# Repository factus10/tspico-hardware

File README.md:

# TS-Pico hardware

Hardware for the TS-Pico, a mass-storage, ROM, and now WiFi/sound expansion card for the Timex Sinclair 2068.

## What the TS-Pico does

The TS-Pico plugs into the TS2068's rear expansion connector, with a Raspberry Pi microcontroller on the card. To the 2068 it looks like memory and I/O ports:

- **ROMs and cartridges.** The card can replace the 2068's HOME ROM and EXROM and act as a DOCK cartridge, serving the images from its own memory. It comes with its own patched 2068 ROM, which knows how to talk to the card.
- **Mass storage.** LOAD and SAVE go to files on a micro SD card instead of tape, and the card also takes `tpi:` commands. The 2068 talks to the card through I/O ports $0E/$0F.
- **Printer.** LPRINT, LLIST and COPY go to the card.

v3 adds WiFi, sound, a joystick port and a display on top of that.

## The boards

| | v2.2 | v2.5 | v2.6 | v3 |
|---|---|---|---|---|
| Status | Shipped 2023 | Prototype, not built | Prototype, not built | Proto1 built and brought up; proto3 is current |
| Controller | Raspberry Pi Pico on socket headers | Pico module soldered on its castellations (a Pico 2 fits) | RP2040 on the board, 2 MB QSPI flash, USB-C | RP2350B on the board, 16 MB QSPI flash, USB-C, PSRAM footprint (8 MB, hand-fitted) |
| Card memory | 512 KB flash (SST39SF040) + 512 KB SRAM, DIP | Same chips, SMT (PLCC flash, SOIC SRAM) | Same DIP chips, socketed | None: the RP2350B serves ROM and DOCK images from its own SRAM with PIO and DMA |
| Construction | Through-hole | All SMT, JLCPCB-assembled | SMT except the two DIP sockets | All SMT except the DE-9 and OLED header |
| Firmware | Shipped TS-Pico firmware | Runs it unchanged | Runs it unchanged | Ported (v2.3.1 runs on v3) |

**v2.2** (`old/`) is the card that shipped in September 2023. It has a Pico on headers, flash and SRAM chips, 74LS glue logic and a 555 power-on reset. The 2068 reads its ROM and cartridge images from the flash or SRAM in 16 slots of 32 KB, and the Pico switches the banks. The micro SD sits on a breakout module and shares three data lines with the bus. A jumper picks the port pair ($00-$0F or $10-$1F). The design is kept here for reference only.

**v2.5** (`hardware-v2.5/`) is the v2.2 circuit redrawn all surface mount, so JLCPCB can assemble it. It uses the v3 board outline and has a push-push micro SD socket. One block is new: **bench programming**, which lets the Pico write a blank soldered flash from USB, with no ROM programmer or 2068 needed.

**v2.6** (`hardware-v2.6/`) is the v2.2 circuit with the RP2040 chip on the board instead of a Pico module. The flash and SRAM go back to DIP-32 chips in sockets, programmed in a ROM programmer as v2.2's were. Proto2 rebuilds the glue logic in 74LVC and replaces the 555 with a TPS3808 reset supervisor.

**v3** (`hardware/`) is a redesign around the RP2350B. It keeps the firmware's view of the bus and adds:

- **Memory without memory chips.** PIO and DMA answer every Z80 memory cycle from the RP2350B's SRAM. Images live as files on the QSPI flash or the SD card, and a slot map file replaces the fixed flash banks.
- **Micro SD** on its own SPI bus, with a current-limited power switch, so a card that latches up can be power-cycled.
- **WiFi:** an ESP32-C3 running Zimodem. The card emulates the TS2050 modem's Intel 8251 at ports $73/$77.
- **Kempston joystick:** a DE-9 (Atari pinout) at port $1F.
- **Stereo audio:** PWM from the RP2350B, mixed with the 2068's SOUND line by an op-amp, out a 3.5 mm jack. It is intended for AY-3-8910 emulation, which the firmware has not scheduled yet.
- **Display:** a 128x64 SSD1309 OLED on I2C (proto3; proto1 and proto2 have a header for a 128x96 SPI module).
- **Tape:** EAR out and SPK/TAP in.
- **Bus control:** the card holds the 2068 in reset until it is ready, instead of a fixed 555 delay. There is also a /WAIT output, which the firmware does not use.
- **Power:** the card runs from the 2068's 5 V or from USB-C alone on the bench.
- **Buttons:** TS Reset, NMI, RUN and BOOTSEL.

The full spec is [docs/v3-architecture.md](docs/v3-architecture.md). Firmware progress is in [docs/v3-firmware-port-plan.md](docs/v3-firmware-port-plan.md).

## Repository

| Folder | What |
|---|---|
| `hardware/` | TS-Pico v3: KiCad 10 project. RP2350B chip-down, surface mount, JLCPCB assembly. See `hardware/README.md`; order files in [v3.0-proto3.1](https://github.com/factus10/tspico-hardware/releases/tag/v3.0-proto3.1). |
| `hardware-v2.5/` | TS-Pico v2.5: the v2.2 circuit all surface mount on the v3 outline, plus bench programming of the flash from the Pico. KiCad 10. See `hardware-v2.5/README.md`; order files in [v2.5-proto1](https://github.com/factus10/tspico-hardware/releases/tag/v2.5-proto1). |
| `hardware-v2.6/` | TS-Pico v2.6: the v2.2 circuit with the RP2040 on the board, SMT except the DIP-32 flash and SRAM (socketed, hand-soldered). KiCad 10. See `hardware-v2.6/README.md`; order files in [v2.6-proto2](https://github.com/factus10/tspico-hardware/releases/tag/v2.6-proto2). |
| `docs/` | [PLAN.md](PLAN.md) (plan), [docs/v3-architecture.md](docs/v3-architecture.md) (interface spec), part mapping, archived variants. |
| `old/` | TS-Pico v2.2: the shipped through-hole design (CircuitStudio project and full fab package, September 2023). Reference only. |

The v3 board (prototype 3). Schematic: [hardware/docs/tspico-v3-schematic.pdf](hardware/docs/tspico-v3-schematic.pdf). PCB layers: [hardware/docs/tspico-v3-pcb.pdf](hardware/docs/tspico-v3-pcb.pdf).

| v3 top | v3 bottom |
|---|---|
|  |  |

| v2.6 | v2.5 |
|---|---|
|  |  |

Firmware lives in [tspico-firmware-build](https://github.com/timex-sinclair-projects/tspico-firmware-build).

## Ordering a board

Ready-to-upload JLCPCB packages (Gerbers, BOM, placement, ordering notes, schematic PDF, renders) are attached to the GitHub releases. All are prototypes. v3 proto1 has been built and brought up (`firmware/bringup/README.md`); proto2 carries its fixes, and proto3 adds a male DE-9 for Atari sticks, a 4-pin header for an I2C SSD1309 OLED and the buttons in a 2x2 block. The others have not been built yet.

| Board | Release |
|---|---|
| v2.6: RP2040 on the board, DIP-32 flash and SRAM in sockets (hand-soldered), 74LVC glue | [v2.6-proto2](https://github.com/factus10/tspico-hardware/releases/tag/v2.6-proto2) (proto1, with 74LS glue: [v2.6-proto1](https://github.com/factus10/tspico-hardware/releases/tag/v2.6-proto1)) |
| v2.5: all surface mount, Pico module, bench programming of the flash | [v2.5-proto1](https://github.com/factus10/tspico-hardware/releases/tag/v2.5-proto1) |
| v3: RP2350B, WiFi, audio, joystick | [v3.0-proto3.1](https://github.com/factus10/tspico-hardware/releases/tag/v3.0-proto3.1): proto3 with board labels, L1 assembled (earlier: [v3.0-proto3](https://github.com/factus10/tspico-hardware/releases/tag/v3.0-proto3), no labels, L1 by hand; [v3.0-proto2.1](https://github.com/factus10/tspico-hardware/releases/tag/v3.0-proto2.1), proto2 with L1 fitted by hand; [v3.0-proto2](https://github.com/factus10/tspico-hardware/releases/tag/v3.0-proto2) assembles L1; proto1, built, before the bring-up fixes: [v3.0-proto1](https://github.com/factus10/tspico-hardware/releases/tag/v3.0-proto1)) |

## Working on the v3 hardware

Requirements: KiCad 10 (`kicad-cli` is used for checks), Python 3.

```bash
python3 hardware/scripts/gen_board.py   # regenerate the edge-connector footprint and board skeleton
hardware/scripts/check.sh               # ERC + DRC, fails on any violation
```

See `hardware/README.md` for the project layout and the geometry the edge connector is built from.

## License

The hardware designs in this repository (`hardware/`, `hardware-v2.5/`, `hardware-v2.6/`, `old/` and the design documents in `docs/`) are released under the [CERN Open Hardware Licence Version 2, Strongly Reciprocal](LICENSE) (CERN-OHL-S-2.0). You may make, modify and sell boards from them. If you distribute a modified design, or boards made from one, you must publish the modified design under the same licence.

**Source Location:** https://github.com/factus10/tspico-hardware. The v2.6 and v3 boards carry this URL, the licence name and the open-source hardware logo on their bottom silkscreen. Boards made from a modified design must carry the location of the modified source instead.

Not covered: the bring-up firmware in `firmware/` is software and is not licensed under CERN-OHL-S. `firmware/bringup/pico_sdk_import.cmake` keeps Raspberry Pi's BSD-3-Clause licence. Zimodem is fetched at build time from its own repository under its own licence. KiCad library parts and 3D models are used under the KiCad libraries' licence.

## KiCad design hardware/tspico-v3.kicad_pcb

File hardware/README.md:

# TS-Pico v3 KiCad project

Status 2026-10-19: prototype 3 ([v3.0-proto3](https://github.com/factus10/tspico-hardware/releases/tag/v3.0-proto3), changes below). Proto1 ([v3.0-proto1](https://github.com/factus10/tspico-hardware/releases/tag/v3.0-proto1)) was built and brought up; proto2 added its fixes (below). Both proto2 and proto3 were routed by `scripts/flow.py` with no hand edits, DRC clean at every severity. ERC: one warning, U4's unused input tied to GND.

**To order:** the JLCPCB upload files (Gerber zip, BOM, placement), ordering notes, schematic PDF and renders are on the [v3.0-proto3.1 release](https://github.com/factus10/tspico-hardware/releases/tag/v3.0-proto3.1): proto3 with the board labels, and L1 assembled by JLCPCB again. U22, J3 and J5 are fitted by hand. [v3.0-proto3](https://github.com/factus10/tspico-hardware/releases/tag/v3.0-proto3) is the same copper without the labels, with L1 fitted by hand. Proto2: [v3.0-proto2.1](https://github.com/factus10/tspico-hardware/releases/tag/v3.0-proto2.1) (L1 by hand) and [v3.0-proto2](https://github.com/factus10/tspico-hardware/releases/tag/v3.0-proto2) (L1 assembled by JLCPCB), same Gerbers. To regenerate them from this folder, run `python3 scripts/gen_fab.py` (output in `fab/jlcpcb/`).

## Proto4 changes (branch `claude/rp2350-inductor-replacement-f42f1a`, not yet tagged)

| Change | Parts | Why |
|---|---|---|
| External core LDO, no inductor | U33 Microne ME6211C12M5G-N (C236672), C53 1 uF input, C20 4.7 uF output; L1 removed | L1 (Abracon AOTA-B201610S3R3-101-T) ran out at JLCPCB twice (0 on 2026-10-12, 1 left on 2026-11-04) and has no substitute. RP2350 datasheet section 6.3.7 / figure 24: VREG_LX (pin 63) open, VREG_FB (pin 65) to GND, VREG_VIN and VREG_AVDD still powered for power-on reset and brown-out. DVDD is 1.2 V, the value the firmware already sets for the 250 MHz bus clock (OpenSpand does the same at 208 MHz). The ME6211 is ±1%, tighter than the on-chip regulator's ±3% at the same setting; 1.2 V is above DVDD's recommended 1.16 V and close to its 1.21 V absolute maximum, as the 1.20 V firmware setting already was. Issue #30 (does 250 MHz run at 1.1 V?) no longer blocks this; it would only matter for a 1.1 V part. |
| C31 moved | C31 left of R28 | U33 sits in its old place above the chip's top-left corner. |

Routed 2026-11-04 by `scripts/flow.py` on its first attempt with no hand edits: 2112 track segments, 401 vias, DRC clean at every severity (no errors, warnings or unconnected items), no tracks on the plane layers. ERC: the one known warning (U4). 40 BOM lines, 142 parts, $14.19/board on 10 boards with fees (proto3.1: $14.68).

Firmware for proto4: the core voltage is fixed, so `vreg_set_voltage()` has no effect (harmless). Set the VREG `HIZ` bit after boot (unlock with `VREG_CTRL.UNLOCK` first): the on-chip regulator still starts at power-up and draws about 400 µA until then. Never put the regulator in low-power mode: the datasheet says it can't be disconnected from DVDD in that mode.

## Proto3 changes

| Change | Parts | Why |
|---|---|---|
| Male DE-9 | J5 CONNFLY DS1037-09MNAKT74-0CC (C75750), footprint `DSUB-9_Pins_Horizontal_…` | Atari sticks (CX-40) end in a female plug, like the 2068's own male ports expect. Proto1/2 had a female footprint; a male connector on it mirrors every pin, putting the stick's ground (pin 8) on pin 7 (JOY_5V, open) so nothing reads. Same body position and holes as proto2. On a proto1/2 board, mount a male connector on the back of the board: turning it over puts each pin on its own pad. |
| Buttons and LED moved | SW3 under SW1, SW4 under SW2; D4/R5 left of the ESP32 | A 1.54 in module on J3 covered BOOTSEL and crowded RUN. |
| I2C OLED header | J3 1x4 (1 GND, 2 +3V3, 3 SCL, 4 SDA), R44/R45 4k7 pull-ups | For a 1.54 in 128x64 SSD1309 I2C module, on I2C1 (GP43 SCL, GP42 SDA). Replaces the 7-pin header for the 1.27 in SSD1351 SPI module. GP34, GP41 and expander P0.2 (with its pull-down R11) are freed. |

## Proto2 changes (from proto1 bring-up and issue #21)

| Change | Parts | Why |
|---|---|---|
| nBE pull-up to +5V_EDGE | R14 2k2 | The 74LVC06 only pulls /BE low; without a pull-up it rose too slowly and a RAM opcode fetch after a served byte read wrong bits. Proto1 boards carry a 2.2k bodge from A29 to +5V. |
| GP8-GP10 pull-ups | R15-R17 10k | nAEN_LO, nAEN_HI, nDATA_OE: the RP2350 resets its pads with pull-downs, so in reset and BOOTSEL all three buffers were enabled and U1/U2 fought on MD. |
| SD socket power switch | U32 SY6280AAC, R42 15k (0.45 A), R43 10k, C52 1u | Socket VDD is now +3V3_SD, switched from XL9555 P0.6 (SD_PWR_EN, off at power-up). A latched card hits the current limit instead of resetting the RP2350B; the firmware can power-cycle a card. R34-R37 moved to +3V3_SD; R38 (detect) stays on +3V3. |
| U22 footprint | SOIC-8 3.9 x 4.9 mm | The APS6404L-3SQR-SN is SOP-8 150 mil (AP Memory package code SN); proto1 had the 208 mil footprint. Still DNP; see `docs/bom-cost-optimization.md` for PSRAM options. |
| L1 fitted by hand | L1 DNP at JLCPCB | The RP2350 core-regulator inductor (Abracon AOTA-B201610S3R3-101-T) was out of stock at JLCPCB and LCSC on 2026-10-12. Raspberry Pi names no substitute: it is the only polarity-marked 0806 part. Fit it with the dot on pad 2 (DVDD, silkscreen dot), the end away from the top edge; the core has no supply until it is on. Gerbers unchanged. From proto3.1 (2026-10-22, 326 in stock) JLCPCB assembles it again. |

Firmware for proto2: set SD_PWR_EN (expander port 0 bit 6) after the detect switch reads a card and before any SPI; return the SD pins to inputs before clearing it.

Sheets are generated by `scripts/gen_<sheet>.py` on top of `scripts/schlib.py`, netlist-style (labels on every pin, no wires). Regenerating a sheet overwrites hand edits, so once a sheet is being edited in KiCad, retire its generator. Spec: [../docs/v3-architecture.md](../docs/v3-architecture.md).

## Files

| File | Purpose |
|---|---|
| `tspico-v3.kicad_pro` | Project. Design rules are JLCPCB 4-layer capable but conservative: 0.127 mm min clearance and track, 0.45/0.2 mm min via, 0.3 mm copper-to-edge. Net classes: Default 0.2 mm track / 0.6-0.3 via, Power 0.5 mm / 0.8-0.4. |
| `tspico-v3.kicad_sch` | Root sheet with eight hierarchical sheets: `interface`, `memory`, `mcu`, `power`, `storage_display`, `wifi`, `audio`, `joystick`. |
| `tspico-v3.kicad_pcb` | 4-layer board (F.Cu, In1 GND, In2 PWR, B.Cu), 1.6 mm, ENIG. Outline and connector generated by `scripts/gen_board.py`. |
| `lib/tspico.pretty/TS2068_EdgeConnector_2x32.kicad_mod` | The 2068 edge connector (generated). |
| `lib/tspico.kicad_sym` | Project symbols (empty so far; ESP32-C3 module and anything not in the stock library go here). |
| `scripts/gen_board.py` | Regenerates the edge-connector footprint and the bare board skeleton (outline, connector, holes, fiducials). Called by `gen_layout.py`. |
| `scripts/gen_layout.py` | Builds the placed board: exports the netlist, loads every footprint from the KiCad or project library, assigns nets, places parts from its `P` table, adds the GND and +3V3 zones. Run with KiCad's bundled Python (`/Applications/KiCad/KiCad.app/Contents/Frameworks/Python.framework/Versions/Current/bin/python3`). **It overwrites `tspico-v3.kicad_pcb`, so once routing starts in KiCad, stop running it and treat the placement table as history.** |
| `scripts/check.sh` | `kicad-cli` ERC and DRC. |
| `scripts/schlib.py`, `scripts/gen_edge_symbol.py`, `scripts/gen_interface.py`, `scripts/gen_memory.py`, `scripts/gen_mcu.py`, `scripts/gen_power.py`, `scripts/gen_storage_display.py`, `scripts/gen_wifi.py`, `scripts/gen_audio.py`, `scripts/gen_joystick.py` | Schematic generators (see above). |
| `scripts/parts.py` | Orderable part table: (Value, footprint) to MPN and LCSC number. `schlib.place()` stamps MPN and LCSC fields on every symbol from it. |
| `bom/tspico-v3-jlcpcb-bom.csv` | JLCPCB-format BOM (Comment, Designator, Footprint, LCSC Part #), regenerated by the command below. |
| `bom/tspico-v3-bom-full.csv` | Same grouping with MPN and quantities. |
| `docs/tspico-v3-schematic.pdf` | Schematic, all nine sheets. |
| `docs/tspico-v3-pcb.pdf` | PCB plot, one page per layer: F.Cu, In1.Cu, In2.Cu, B.Cu, F/B silkscreen, F/B fab (DNP parts crossed out). Bottom layers are not mirrored. |
| `renders/` | 3D renders (top, bottom, isometric). |
| `fab/` | Plot output directory (ignored by git). |

## Edge connector geometry

Measured from the v2.2 fab Gerbers (`../old/tsPico2_2Fab/Gerber/tsPico.GTL`, `.GBL`, `.Outline`):

| Item | Value |
|---|---|
| Board | 130.00 x 64.25 mm, 1.6 mm (v2.2 was 100 mm tall; v3 body is 56 mm plus the 8.25 mm tongue) |
| Body | 130.00 x 64.00 mm |
| Tongue | 83.66 mm wide, 8.25 mm deep, left edge 18.48 mm from the board's left edge, 1.0 mm corner chamfers |
| Positions | 32 at 2.54 mm pitch, 31 fingers per side |
| Keying slot | position 6, 2.03 mm wide, 8.26 mm deep |
| Fingers | 1.651 x 8.255 mm (65 x 325 mil), first finger centre 2.52 mm from the tongue's left edge, bottom edge 0.32 mm above the tongue edge |

Pad names are `A1`..`A32` on F.Cu and `B1`..`B32` on B.Cu (no A6/B6), following the TS2068 Technical Manual table 2.4.1-1. Position 1 is at the left when the board is viewed from the top with the connector at the bottom.

**Side A is the top (component) side, confirmed:** side A (GND, EAR, D7, ..., SOUND) is on the top and side B (+15V, +5V, address bus, video) on the bottom. Proto1 proved it in a 2068 on 2026-10-07 ([`firmware/bringup/README.md`](../firmware/bringup/README.md)). In shadow mode it logged every address the Z80 read through the side-B fingers, the boot log matching the ROM exactly. It then served the HOME ROM onto side A, with /MREQ and /RD timing each read, /BE on A29 and the data on D0-D7, and the 2068 booted to the card's "TS-Pico v3 ROM" banner. With the sides swapped, the address fingers would sit on data and control lines and none of that could work. This also matches how the v2.2 layout routes +5V (bottom trace from the fourth finger).

Fab notes for the fingers: hard gold over the fingers if the fab offers it (ENIG otherwise), 30 degree bevel on the tongue edge, no copper within 0.3 mm of the slot.

## Stock library parts already identified

RP2350B symbol (`MCU_RaspberryPi`), `Package_DFN_QFN:QFN-80-1EP_10x10mm_P0.4mm_EP3.4x3.4mm`, `TSPico:microSD_TF-01A` (to be drawn from the HRO TF-01A drawing), `Connector_Dsub:DSUB-9_*`, `Connector_USB:USB_C_Receptacle_HRO_TYPE-C-31-M-12`, SOIC/TSSOP logic packages, `Button_Switch_SMD:SW_SPST_PTS645Sx43SMTR92`, `Connector_Audio:Jack_3.5mm_CUI_SJ-352x-SMT_Horizontal`, `Crystal:Crystal_SMD_3225-4Pin_3.2x2.5mm`.

All parts used so far have stock symbols and footprints (the APS6404L PSRAM is in `Memory_RAM`, the ESP32-C3-WROOM-02 in `RF_Module`).

## Regenerating the BOM

```bash
cd hardware
KC=/Applications/KiCad/KiCad.app/Contents/MacOS/kicad-cli
$KC sch export bom --output bom/tspico-v3-jlcpcb-bom.csv --fields "Value,Reference,Footprint,LCSC" --labels "Comment,Designator,Footprint,LCSC Part #" --group-by "Value,Footprint" --exclude-dnp tspico-v3.kicad_sch
```

Part choices are priced against JLCPCB's catalog with `python3 scripts/jlc_price.py --boards 10`; the reasoning for each substitution is in `docs/bom-cost-optimization.md` (2026-09-17: parts + fees per board went from $32.95 to $14.93 on a 10-board run, to $14.48 after the DMA option was dropped; fitted logic packages from 16 to 7). The board was laid out again for these parts on 2026-09-17 (see the routing section).

## Fab outputs

`python3 scripts/gen_fab.py` writes `fab/jlcpcb/`: `tspico-v3-gerbers.zip` (4-layer Gerbers + Excellon drill), `tspico-v3-bom.csv` and `tspico-v3-cpl.csv` (JLCPCB assembly format), and refreshes the two BOMs in `bom/`. `fab/NOTES.md` lists what to check on upload (rotations of QFN/SOT/connector parts need checking in JLC's placement preview; J3 and J5 are through-hole).

## Schematic and PCB PDFs, renders

Regenerate after a board or schematic change (from `hardware/`):

```bash
KC=/Applications/KiCad/KiCad.app/Contents/MacOS/kicad-cli
$KC sch export pdf -o docs/tspico-v3-schematic.pdf tspico-v3.kicad_sch
$KC pcb export pdf --mode-multipage --ibt --scale 0 --cdnp -l F.Cu,In1.Cu,In2.Cu,B.Cu,F.Silkscreen,B.Silkscreen,F.Fab,B.Fab --cl Edge.Cuts -o docs/tspico-v3-pcb.pdf tspico-v3.kicad_pcb
$KC pcb render --side top --quality high -w 2384 -h 1376 --zoom 1.1 -o renders/tspico-v3-top.png tspico-v3.kicad_pcb
$KC pcb render --side bottom --quality high -w 2384 -h 1376 --zoom 1.1 -o renders/tspico-v3-bottom.png tspico-v3.kicad_pcb
$KC pcb render --side top --quality high -w 2384 -h 1568 --rotate '-45,0,45' --perspective -o renders/tspico-v3-iso.png tspico-v3.kicad_pcb
```

Parts without a 3D model in the KiCad library (the four buttons, USB-C, micro SD socket, audio jack) show as bare pads in the renders; U22 is DNP.

## Layout notes

- Body 130 x 56 mm (the register row of the first layout is gone). Left edge, top to bottom: ESP32-C3 antenna, USB-C, micro SD. The TF-01A socket's shell is flush with the board edge (its shield pads sit 3 mm back, so nothing needs edge clearance). Right edge: 3.5 mm jack in the corner, DE-9 below it.
- Top edge: buttons in a 2x2 block on 0.5 in centres (top row TS Reset, NMI; below them RUN, BOOTSEL; proto1/2 had all four in a row), then the OLED header. The module on J3 covers everything right of the buttons, so nothing there may be taller than its standoff. The LED (D4, R5) sits left of the ESP32, between the mounting hole and the USB-C socket. A bottom-layer keepout (no tracks or vias) sits under the RP2350B.
- Row above the fingers: data U3, high address byte U2 directly over fingers A15-A8, control U4 (U3 is turned 180 degrees from the others: its A side is the Z80 side so DIR can be /RD itself). Row above that: low address byte U1 over U2, fed from fingers A0-A3 on the left and A7-A4 on the right along the bottom layer, then strobe OR gates U6 and open-drain drivers U7. Both address buffers put plain bytes on MD0-MD7, so the firmware sees ordinary addresses. I2C expander U15 and the joystick conditioning network sit beside the DE-9; audio and the two LDOs above them.
- RP2350B core supply (proto4): the ME6211C12 LDO U33 sits above the chip's top-left corner, input cap C53 to its right, output cap C20 to its left. Its 0.3 mm output track drops straight down beside R28 and enters the pad ring diagonally at the corner between pins 60 and 61, joining the DVDD spine under the package. VREG_LX is open, VREG_FB runs to the PGND via, VIN goes straight into C22 and the AVDD filter R28/C39 sits above, as in "Hardware design with RP2350" figure 4. (Proto1-3 had the design guide's switcher with L1 left of C20/C22.)
- Crystal 6.5 mm from its pins with R20 between chip and crystal; XOUT_R runs under the crystal to pad 3. XIN and XOUT drop one pad lane after leaving the chip so DVDD pin 32 has room for its via.
- Before ordering: check the D-sub footprint against the CONNFLY DS1037 drawing, check `lib/tspico.pretty/microSD_TF-01A` against the part's drawing (generated from LCSC's land pattern). (TF-01A card detect: low = card in, confirmed on proto1.)

## Routing flow and state

```bash
cd hardware
PY=/Applications/KiCad/KiCad.app/Contents/Frameworks/Python.framework/Versions/Current/bin/python3
$PY scripts/gen_layout.py     # placement, keepouts, planes (discards all routing)
$PY scripts/preroute.py       # locked hand routes: core LDO and regulator pins, crystal, DVDD spine, inner supply links, bottom-row fan
$PY scripts/autoroute.py --passes 100     # jar from $FREEROUTING_JAR (or --jar); about 25 minutes
$PY scripts/finish.py         # widen necked tracks, join orphan supply islands, retry open nets, drop unused vias and stubs
$PY scripts/silk.py           # place reference designators clear of pads, silk and the edge; trim outlines at the edge
$PY scripts/labels.py v3      # board name on top; name, URL, licence and OSHW logo on the bottom
```

Or all five in one command, which is the way to run it:

```bash
$PY scripts/flow.py                       # jar from $FREEROUTING_JAR (or --jar); 10 to 15 minutes per attempt, up to 3 attempts
```

Freerouting does not give the same result twice from the same input. Before U1's address pins had their pre-routed via fan (below), about one run in three left one of them (A3, A5) sealed in behind its neighbours' vias; with the fan, three runs out of three closed on the first attempt. The safety net stays: if a signal net is left open, `finish.py` tries lifting the neighbours' copper around the pin, routing the open net and putting the neighbours back, but refuses a result that needs more than three vias per net (the only way out of such a pocket has been a 9-via, 70 mm detour). If the board still is not clean `finish.py` exits non-zero and `flow.py` routes again from the placement, keeping the failed board as `fab/route/attempt-N.kicad_pcb`.

Rules: 0.15 mm signal tracks (the router may neck down to 0.11 mm in a squeeze; board minimum 0.1 mm, JLCPCB's is 0.09), 0.4 mm on the 5 V rails and +3V3_WIFI, 0.127 mm clearance, every via 0.6/0.3 mm (JLCPCB's no-surcharge size; the ESP32 footprint's 0.2 mm thermal vias are opened to 0.3 mm by `gen_layout.py`). The pre-stitch step skips the RP2350B's pins: a via 0.9 mm out of a 0.4 mm pitch pin blocks both neighbours' escape lanes. Its exposed pad gets five ground vias.

What `preroute.py` fixes in place before the autorouter runs, because the router handles a fully used 0.4 mm pitch QFN badly (whichever pins it leaves for last end up sealed behind its own vias):

- the core LDO and the on-chip regulator's pins, and the crystal, as above;
- the **DVDD spine**: 0.25 mm track under the package from the LDO's entry at the top-left corner to DVDD pins 51, 10 and 32 (only the first 3 mm at the pins is 0.15 mm), and pin 51's 100 nF 2 mm from its pin;
- the 3.3 V supply pins linked in groups under the package, each group with one via: 50 to corner pin 41, 68/69 to 76 to pin 5, 24 to 29;
- the **bottom pad row** (pins 1-20, all used) as a deterministic fan: straight out to a staggered depth, a 45 degree turn, and a via on a common line at 0.75 mm spacing, which is the tightest legal pattern for 0.6 mm vias at 0.4 mm pitch.
- **U1's Z80-side pins** (A0-A7): each runs straight in under U1's body to its own via, in two staggered rows 1.26 and 2.06 mm from the pads. U1's bottom pad row faces U2's top row across a 0.8 mm gap, so these pins can only leave under U1, and their fingers are on the bottom layer, so each needs a via anyway. Neighbouring vias are 1.03 mm apart, and a track on either layer still passes between two vias of the near row.

State on 2026-09-17 (DMA option dropped, address buffers delivering plain bytes, audio and joystick passives respaced for silkscreen, U1 address fan pre-routed): **fully routed, DRC clean at every severity (no errors, no warnings, no unconnected items)**, no tracks on either plane layer. 2073 track segments, 378 vias, all 0.6/0.3 mm, no track under 0.13 mm. Produced by `flow.py` on its first attempt with no hand edits. (Run DRC on the board where it sits: a copy outside the project folder is checked against KiCad's default rules and reports hundreds of false clearance errors.)

Silkscreen: `silk.py` sets designators to 0.8 mm text and tries positions around each part until one clears pads, other silk, other parts and the board edge; rows of equal parts all get the label on the same side (above a flat part, to the right of an upright one), and a hidden designator gets a second chance by moving a neighbour's. The layout leaves room for this: passive rows are 3.2 mm apart in the audio block, 2.7 mm in the SD pull-ups, and the joystick RC columns are 2.6 mm apart. 139 of 140 designators are on silk; only C39 (the VREG_AVDD capacitor, boxed in by the design guide's regulator layout) is hidden, and it is on F.Fab with all the others. Outlines of edge connectors that overhang the board are trimmed where they cross the edge.

Board labels: `labels.py` (also run by `flow.py`) puts "TS-Pico v3" on the top silkscreen above the left end of the fingers. On the bottom it puts the name, the repository URL (the CERN-OHL-S Source Location), the licence and the OSHW logo. It only touches its own group of silkscreen items, so it can be rerun on a routed board, and it refuses to save if a label would land on a pad, a courtyard or other silk. `labels.py v2.6` does the same for `../hardware-v2.6/`.

Rerunning `autoroute.py` continues from the current routing (it exports existing tracks); `--fresh` starts over. Do not rerun `gen_layout.py`: it rebuilds the board from placement and discards routing.

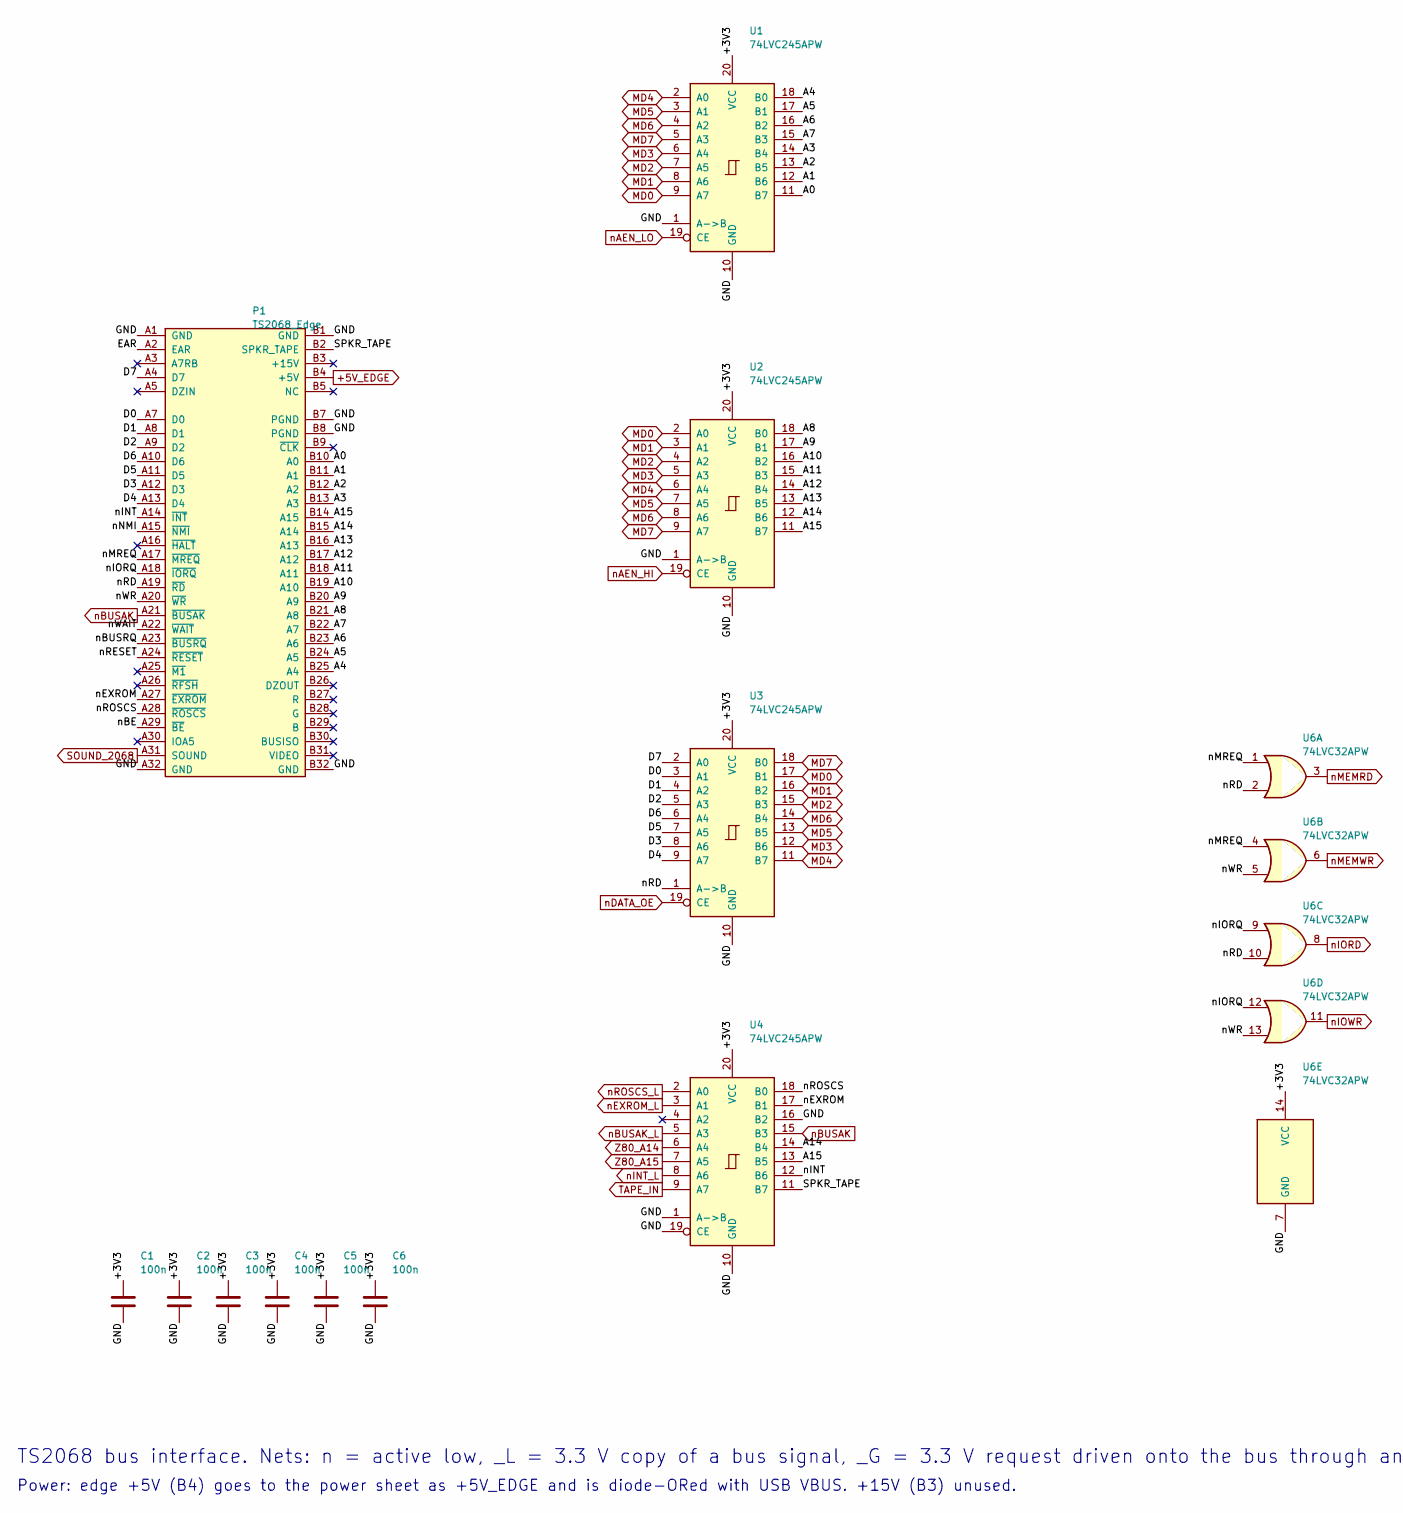
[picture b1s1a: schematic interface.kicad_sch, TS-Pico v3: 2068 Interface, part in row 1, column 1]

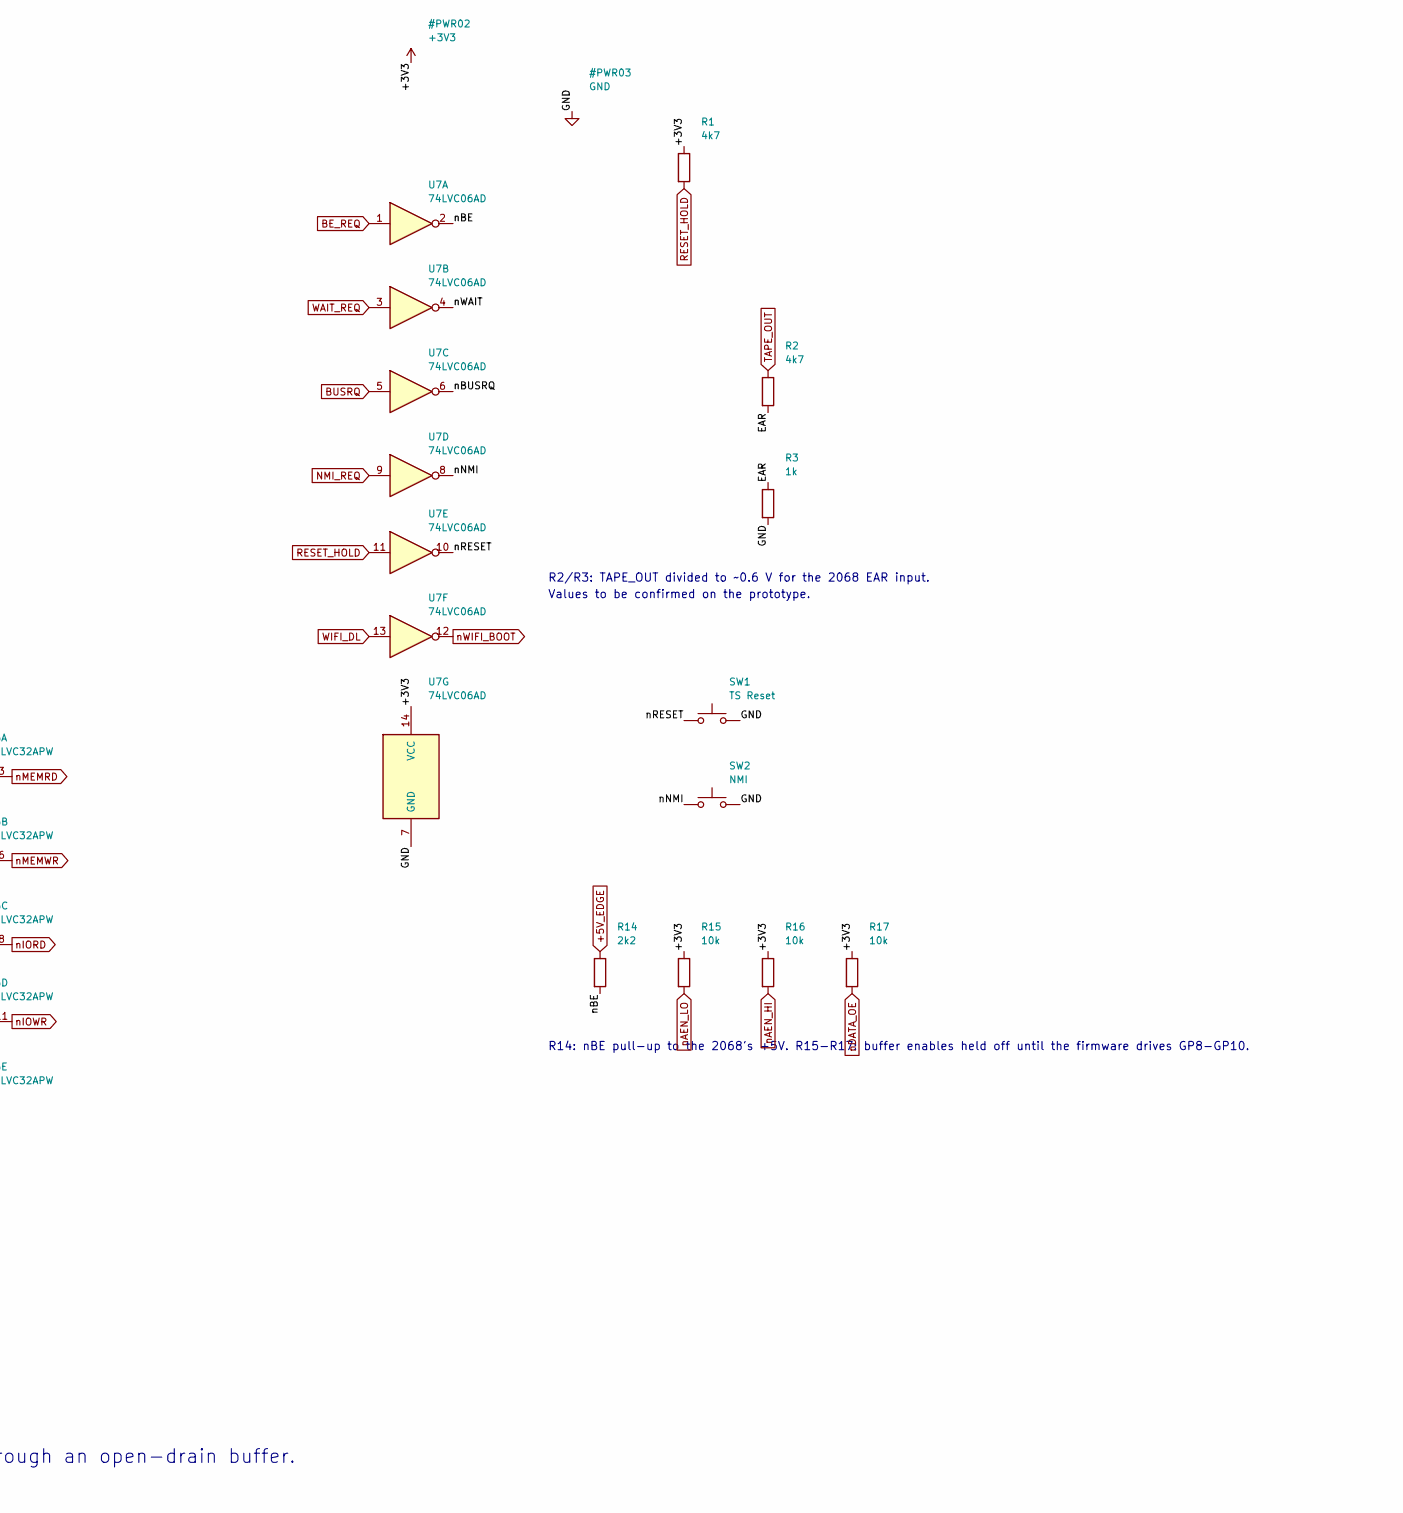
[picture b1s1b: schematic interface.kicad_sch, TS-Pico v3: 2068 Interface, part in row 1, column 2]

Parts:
C1, C2, C3, C4, C5, C6: 100n; C_0603_1608Metric; MPN CC0603KRX7R9BB104; LCSC C14663
P1: TS2068_Edge; TS2068_EdgeConnector_2x32
R1, R2: 4k7; R_0603_1608Metric; MPN 0603WAF4701T5E; LCSC C23162
R3: 1k; R_0603_1608Metric; MPN 0603WAF1001T5E; LCSC C21190
R14: 2k2; R_0603_1608Metric; MPN 0603WAF2201T5E; LCSC C4190
R15, R16, R17: 10k; R_0603_1608Metric; MPN 0603WAF1002T5E; LCSC C25804
SW1: TS Reset; SW_Push_1P1T_XKB_TS-1187A; MPN TS-1187A-B-A-B; LCSC C318884
SW2: NMI; SW_Push_1P1T_XKB_TS-1187A; MPN TS-1187A-B-A-B; LCSC C318884
U1, U2, U3, U4: 74LVC245APW; TSSOP-20_4.4x6.5mm_P0.65mm; MPN 74LVC245APW,118; LCSC C6082
U6: 74LVC32APW; TSSOP-14_4.4x5mm_P0.65mm; MPN 74LVC32APW,118; LCSC C6087
U7: 74LVC06AD; SOIC-14_3.9x8.7mm_P1.27mm; MPN EM74LVC06AD; LCSC C49188178

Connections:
+3V3: C1.1, C2.1, C3.1, C4.1, C5.1, C6.1, R1.1, R15.1, R16.1, R17.1, U1.20 (VCC), U2.20 (VCC), U3.20 (VCC), U4.20 (VCC), U6.14 (VCC), U7.14 (VCC); also elsewhere on the board
+5V_EDGE: P1.B4 (+5V), R14.1; also elsewhere on the board
/2068 Interface/A0: P1.B10 (A0), U1.11 (B7)
/2068 Interface/A1: P1.B11 (A1), U1.12 (B6)
/2068 Interface/A2: P1.B12 (A2), U1.13 (B5)
/2068 Interface/A3: P1.B13 (A3), U1.14 (B4)
/2068 Interface/A4: P1.B25 (A4), U1.18 (B0)
/2068 Interface/A5: P1.B24 (A5), U1.17 (B1)
/2068 Interface/A6: P1.B23 (A6), U1.16 (B2)
/2068 Interface/A7: P1.B22 (A7), U1.15 (B3)
/2068 Interface/A8: P1.B21 (A8), U2.18 (B0)
/2068 Interface/A9: P1.B20 (A9), U2.17 (B1)
/2068 Interface/A10: P1.B19 (A10), U2.16 (B2)
/2068 Interface/A11: P1.B18 (A11), U2.15 (B3)
/2068 Interface/A12: P1.B17 (A12), U2.14 (B4)
/2068 Interface/A13: P1.B16 (A13), U2.13 (B5)
/2068 Interface/A14: P1.B15 (A14), U2.12 (B6), U4.14 (B4)
/2068 Interface/A15: P1.B14 (A15), U2.11 (B7), U4.13 (B5)
/2068 Interface/D0: P1.A7 (D0), U3.3 (A1)
/2068 Interface/D1: P1.A8 (D1), U3.4 (A2)
/2068 Interface/D2: P1.A9 (D2), U3.5 (A3)
/2068 Interface/D3: P1.A12 (D3), U3.8 (A6)
/2068 Interface/D4: P1.A13 (D4), U3.9 (A7)
/2068 Interface/D5: P1.A11 (D5), U3.7 (A5)
/2068 Interface/D6: P1.A10 (D6), U3.6 (A4)
/2068 Interface/D7: P1.A4 (D7), U3.2 (A0)
/2068 Interface/EAR: P1.A2 (EAR), R2.2, R3.1
/2068 Interface/SPKR_TAPE: P1.B2 (SPKR_TAPE), U4.11 (B7)
/2068 Interface/nBE: P1.A29 (~BE), R14.2, U7.2
/2068 Interface/nBUSRQ: P1.A23 (~BUSRQ), U7.6
/2068 Interface/nEXROM: P1.A27 (~EXROM), U4.17 (B1)
/2068 Interface/nINT: P1.A14 (~INT), U4.12 (B6)
/2068 Interface/nIORQ: P1.A18 (~IORQ), U6.9, U6.12
/2068 Interface/nMREQ: P1.A17 (~MREQ), U6.1, U6.4
/2068 Interface/nNMI: P1.A15 (~NMI), SW2.1, U7.8
/2068 Interface/nRD: P1.A19 (~RD), U3.1 (A->B), U6.2, U6.10
/2068 Interface/nRESET: P1.A24 (~RESET), SW1.1, U7.10
/2068 Interface/nROSCS: P1.A28 (~ROSCS), U4.18 (B0)
/2068 Interface/nWAIT: P1.A22 (~WAIT), U7.4
/2068 Interface/nWR: P1.A20 (~WR), U6.5, U6.13
BE_REQ: U7.1; also elsewhere on the board
BUSRQ: U7.5; also elsewhere on the board
MD0: U1.9 (A7), U2.2 (A0), U3.17 (B1); also elsewhere on the board
MD1: U1.8 (A6), U2.3 (A1), U3.16 (B2); also elsewhere on the board
MD2: U1.7 (A5), U2.4 (A2), U3.15 (B3); also elsewhere on the board
MD3: U1.6 (A4), U2.5 (A3), U3.12 (B6); also elsewhere on the board
MD4: U1.2 (A0), U2.6 (A4), U3.11 (B7); also elsewhere on the board
MD5: U1.3 (A1), U2.7 (A5), U3.13 (B5); also elsewhere on the board
MD6: U1.4 (A2), U2.8 (A6), U3.14 (B4); also elsewhere on the board
MD7: U1.5 (A3), U2.9 (A7), U3.18 (B0); also elsewhere on the board
NMI_REQ: U7.9; also elsewhere on the board
RESET_HOLD: R1.2, U7.11; also elsewhere on the board
SOUND_2068: P1.A31 (SOUND); also elsewhere on the board
TAPE_IN: U4.9 (A7); also elsewhere on the board
TAPE_OUT: R2.1; also elsewhere on the board
WAIT_REQ: U7.3; also elsewhere on the board
WIFI_DL: U7.13; also elsewhere on the board
Z80_A14: U4.6 (A4); also elsewhere on the board
Z80_A15: U4.7 (A5); also elsewhere on the board
nAEN_HI: R16.2, U2.19 (CE); also elsewhere on the board
nAEN_LO: R15.2, U1.19 (CE); also elsewhere on the board
nBUSAK: P1.A21 (~BUSAK), U4.15 (B3)
nBUSAK_L: U4.5 (A3); also elsewhere on the board
nDATA_OE: R17.2, U3.19 (CE); also elsewhere on the board
nEXROM_L: U4.3 (A1); also elsewhere on the board
nINT_L: U4.8 (A6); also elsewhere on the board
nIORD: U6.8; also elsewhere on the board
nIOWR: U6.11; also elsewhere on the board
nMEMRD: U6.3; also elsewhere on the board
nMEMWR: U6.6; also elsewhere on the board
nROSCS_L: U4.2 (A0); also elsewhere on the board
nWIFI_BOOT: U7.12; also elsewhere on the board

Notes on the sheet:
TS2068 bus interface. Nets: n = active low, _L = 3.3 V copy of a bus signal, _G = 3.3 V request driven onto the bus through an open-drain buffer.
Power: edge +5V (B4) goes to the power sheet as +5V_EDGE and is diode-ORed with USB VBUS. +15V (B3) unused.
R2/R3: TAPE_OUT divided to ~0.6 V for the 2068 EAR input.
Values to be confirmed on the prototype.
R14: nBE pull-up to the 2068's +5V. R15-R17: buffer enables held off until the firmware drives GP8-GP10.

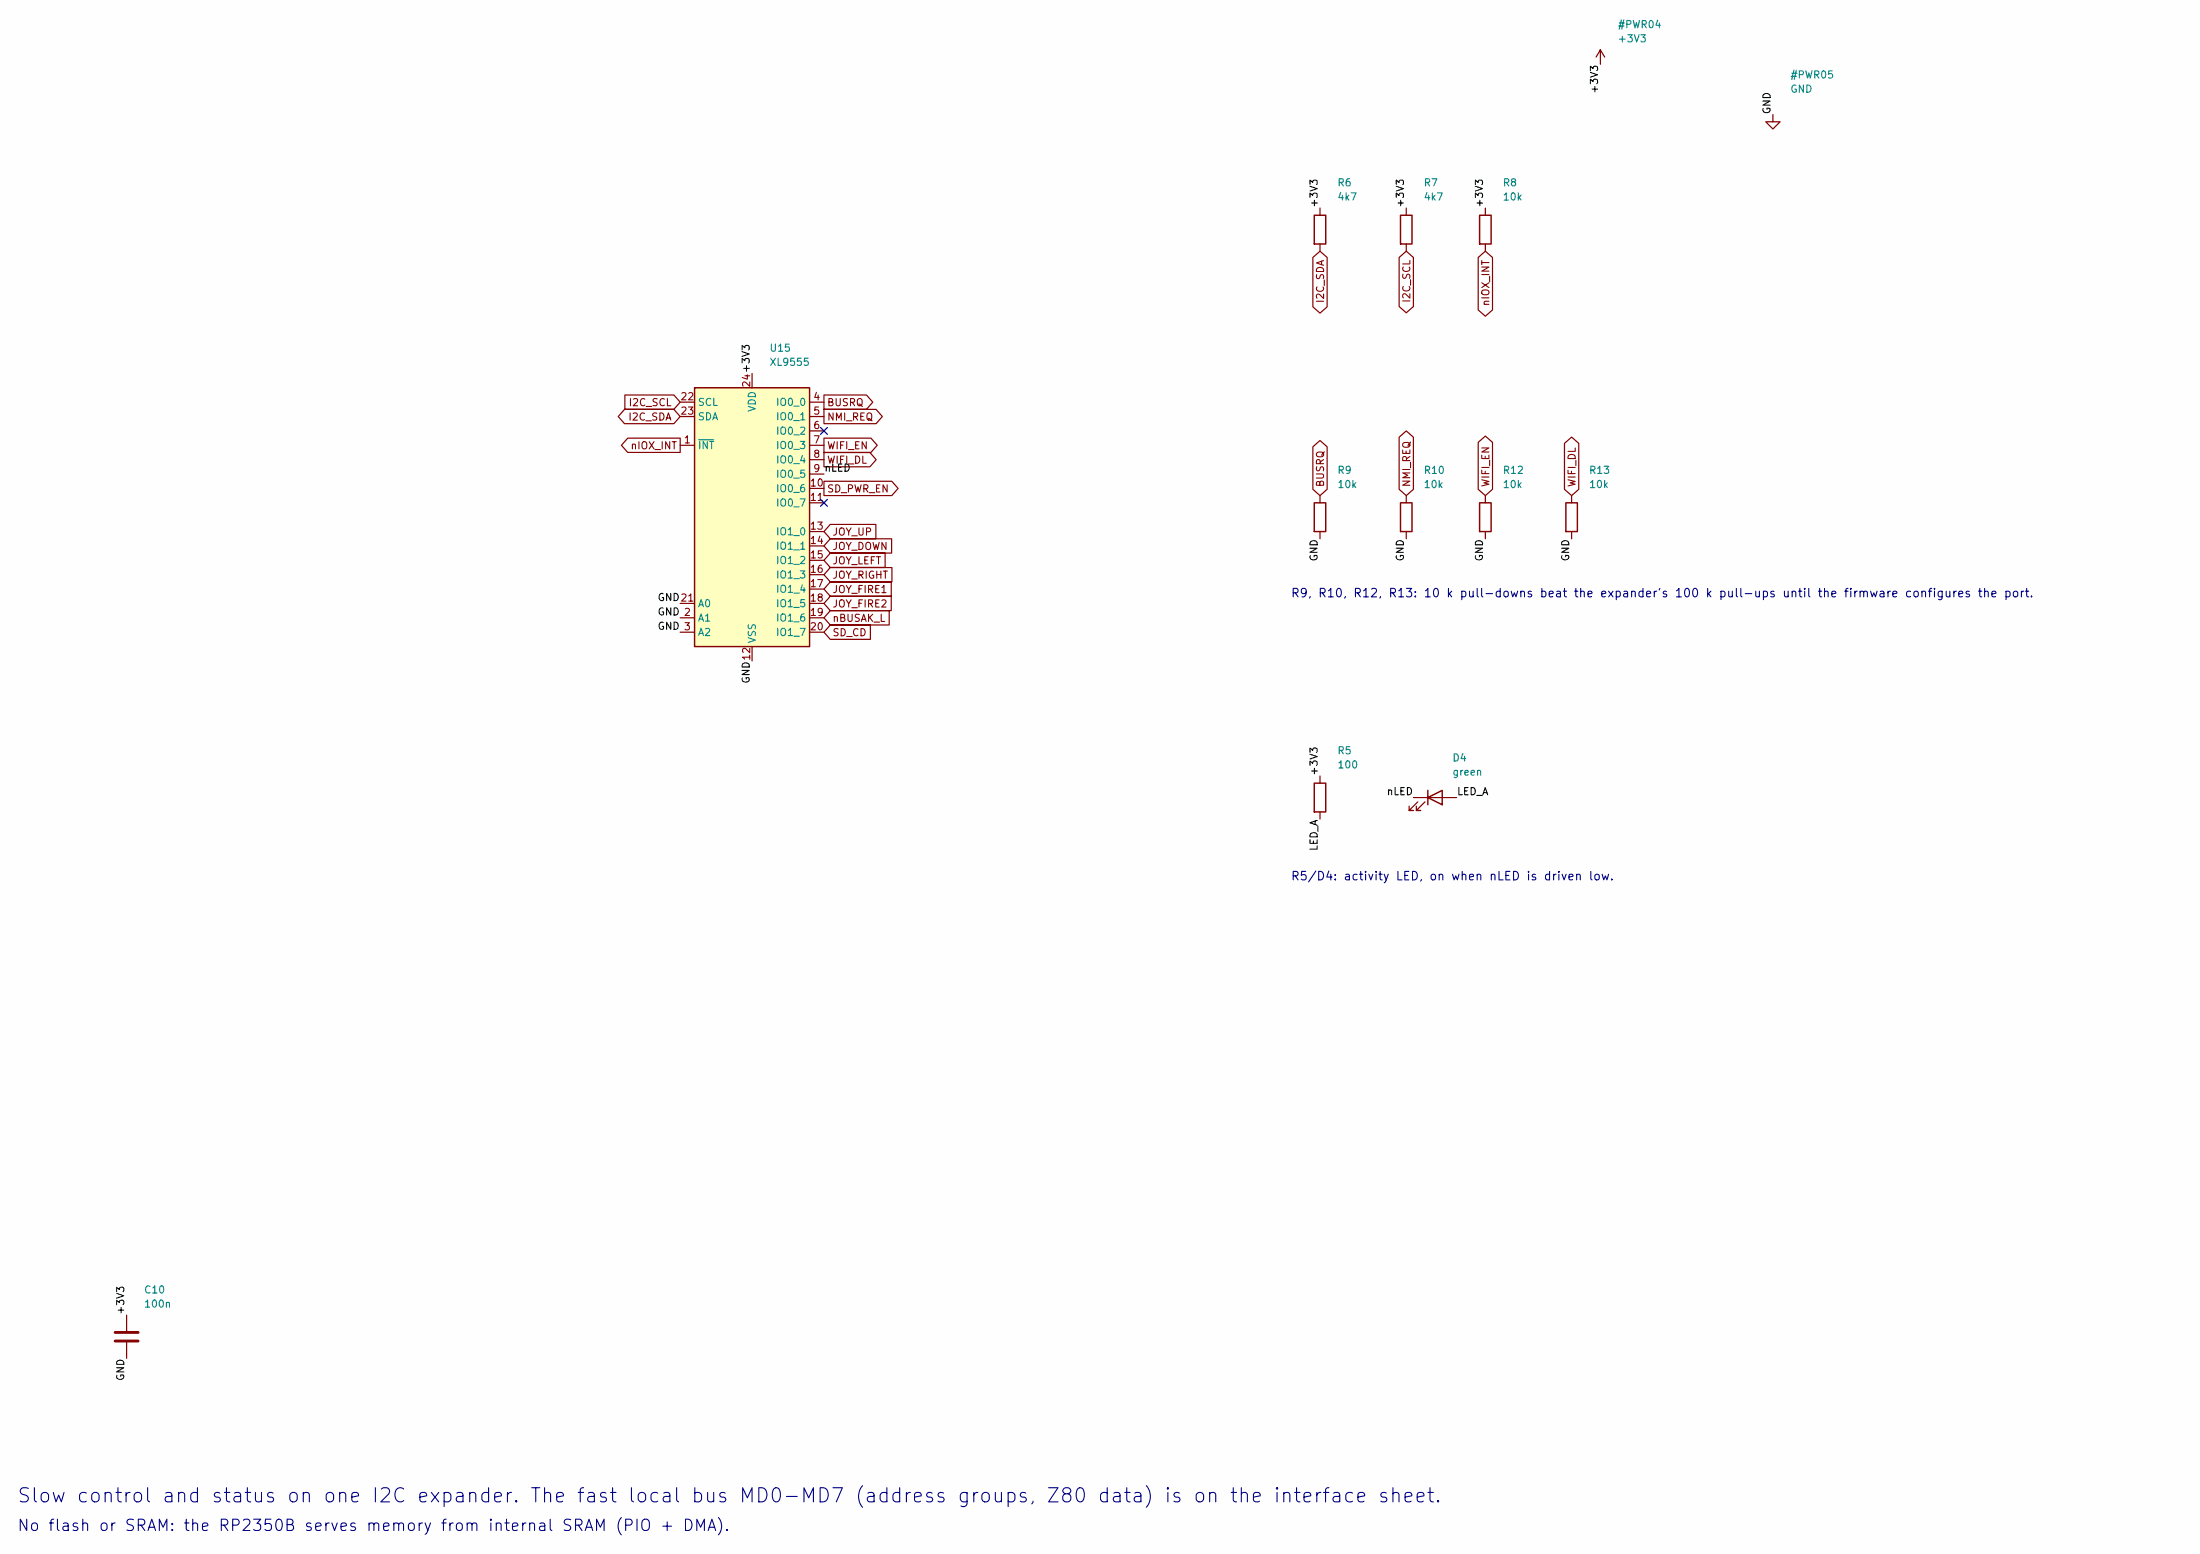
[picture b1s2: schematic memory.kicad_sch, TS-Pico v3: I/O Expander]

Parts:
C10: 100n; C_0603_1608Metric; MPN CC0603KRX7R9BB104; LCSC C14663
D4: green; LED_0805_2012Metric; MPN KT-0805G; LCSC C2297
R5: 100; R_0603_1608Metric; MPN 0603WAF1000T5E; LCSC C22775
R6, R7: 4k7; R_0603_1608Metric; MPN 0603WAF4701T5E; LCSC C23162
R8, R9, R10, R12, R13: 10k; R_0603_1608Metric; MPN 0603WAF1002T5E; LCSC C25804
U15: XL9555; TSSOP-24_4.4x7.8mm_P0.65mm; MPN XL9555; LCSC C609791

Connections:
+3V3: C10.1, R5.1, R6.1, R7.1, R8.1, U15.24 (VDD); also elsewhere on the board
/Local Bus and Registers/LED_A: D4.2 (A), R5.2
/Local Bus and Registers/nLED: D4.1 (K), U15.9 (IO0_5)
BUSRQ: R9.1, U15.4 (IO0_0); also elsewhere on the board
I2C_SCL: R7.2, U15.22 (SCL); also elsewhere on the board
I2C_SDA: R6.2, U15.23 (SDA); also elsewhere on the board
JOY_DOWN: U15.14 (IO1_1); also elsewhere on the board
JOY_FIRE1: U15.17 (IO1_4); also elsewhere on the board
JOY_FIRE2: U15.18 (IO1_5); also elsewhere on the board
JOY_LEFT: U15.15 (IO1_2); also elsewhere on the board
JOY_RIGHT: U15.16 (IO1_3); also elsewhere on the board
JOY_UP: U15.13 (IO1_0); also elsewhere on the board
NMI_REQ: R10.1, U15.5 (IO0_1); also elsewhere on the board
SD_CD: U15.20 (IO1_7); also elsewhere on the board
SD_PWR_EN: U15.10 (IO0_6); also elsewhere on the board
WIFI_DL: R13.1, U15.8 (IO0_4); also elsewhere on the board
WIFI_EN: R12.1, U15.7 (IO0_3); also elsewhere on the board
nBUSAK_L: U15.19 (IO1_6); also elsewhere on the board
nIOX_INT: R8.2, U15.1 (~INT); also elsewhere on the board

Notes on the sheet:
Slow control and status on one I2C expander. The fast local bus MD0-MD7 (address groups, Z80 data) is on the interface sheet.
No flash or SRAM: the RP2350B serves memory from internal SRAM (PIO + DMA).
R9, R10, R12, R13: 10 k pull-downs beat the expander's 100 k pull-ups until the firmware configures the port.
R5/D4: activity LED, on when nLED is driven low.
